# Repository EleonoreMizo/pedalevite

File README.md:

### We have moved!

**This page is now dead, there will not be any update anymore.**

**The new page is hosted here: https://gitlab.com/EleonoreMizo/pedalevite/**  
**Git repository address: https://gitlab.com/EleonoreMizo/pedalevite.git**

Please update your bookmarks! Repository is kept here for consistency with other projects but probably not indefinitely.

Pédale Vite — Multi-FX pedalboard
=================================

**Pédale Vite** is a DIY multi-FX pedalboard for guitar, bass or any other electric instrument.

It is based on a Raspberry Pi 4 and uses a custom audio board.

Key features:

- A large collection of effects within a single box: distortion, chorus, flanger, delay, reverb…
- Programs containing any free combination of the above effects
- 12 footswitches to activate the programs or other functionalities
- Fast and smooth transition between programs
- Up to 3 expression pedals to drive effects like wha, volume, LFOs…
- Infinite modulation possibilities
- Free effect routing
- Designed for stage and regular transport
- Silent and accurate tuner activated with a footswitch
- Standalone, no need for any external computer
- Building is easy and simple, can be reproduced and adapted by any person without specific skill
- Free software and hardware design
- And much more…

More information [here](http://ldesoras.free.fr/doc/articles/pedale-vite/pedale-vite-en.html).

The [/doc/](/doc/) folder contains everything you need to build the pedalboard.

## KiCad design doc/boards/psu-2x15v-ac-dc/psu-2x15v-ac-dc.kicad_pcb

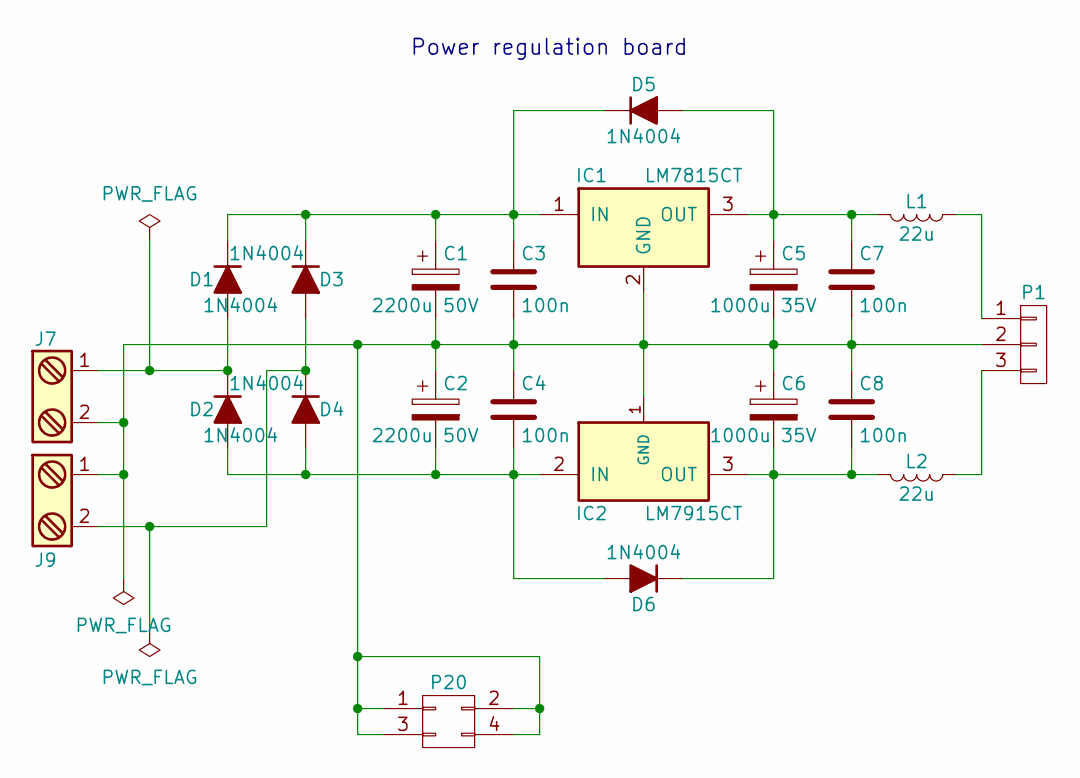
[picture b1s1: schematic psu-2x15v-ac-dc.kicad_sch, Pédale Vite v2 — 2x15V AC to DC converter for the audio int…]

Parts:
C1, C2: 2200u 50V; CP_Radial_D18.0mm_P7.50mm
C3, C4, C7, C8: 100n; C_Disc_D3.4mm_W2.1mm_P2.50mm
C5, C6: 1000u 35V; CP_Radial_D12.5mm_P5.00mm
D1, D2, D3, D4, D5, D6: 1N4004; D_DO-41_SOD81_P7.62mm_Horizontal
IC1: LM7815CT; TO-220_Vertical
IC2: LM7915CT; TO-220_Vertical
J7, J9: Screw_Terminal_1x02; TerminalBlock_Pheonix_MKDS1.5-2pol
L1, L2: 22u; Neosid_Inductor_Sd8
P1: CONN_01X03; Molex_KK-6410-03_03x2.54mm_Straight
P20: CONN_02X02; Pin_Header_Straight_2x02_Pitch2.54mm

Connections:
unnamed: C1.1, C3.1, D1.1 (K), D3.1 (K), D5.1 (K), IC1.1 (IN)
unnamed: C1.2, C2.1, C3.2, C4.1, C5.2, C6.1, C7.2, C8.1, IC1.2 (GND), IC2.1 (GND), J7.2, J9.1, P1.2, P20.1, P20.2, P20.3, P20.4
unnamed: C2.2, C4.2, D2.2 (A), D4.2 (A), D6.2 (A), IC2.2 (IN)
unnamed: C5.1, C7.1, D5.2 (A), IC1.3 (OUT), L1.2
unnamed: C6.2, C8.2, D6.1 (K), IC2.3 (OUT), L2.2
unnamed: D1.2 (A), D2.1 (K), J7.1
unnamed: D3.2 (A), D4.1 (K), J9.2
unnamed: L1.1, P1.1
unnamed: L2.1, P1.3

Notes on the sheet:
Power regulation board

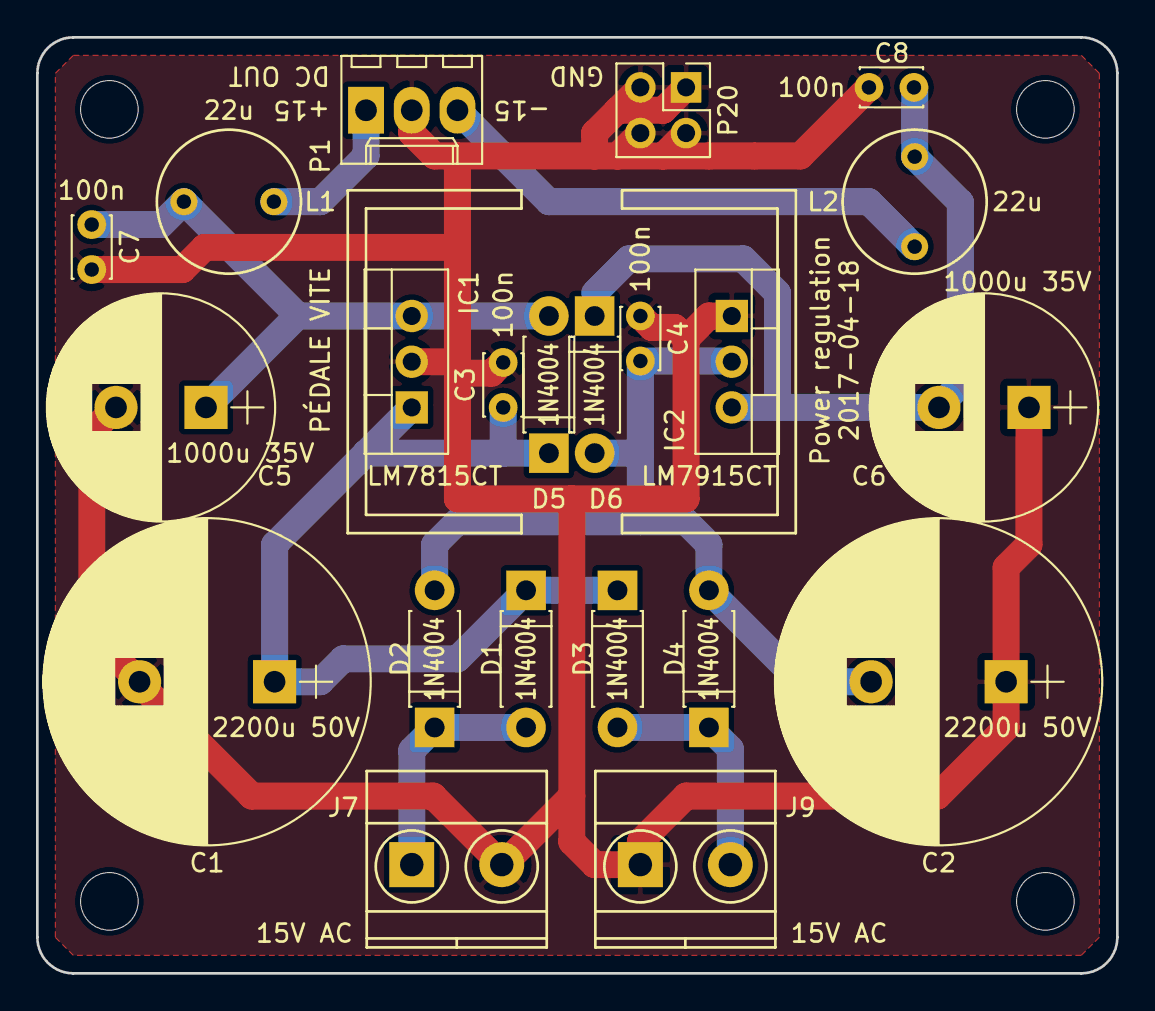
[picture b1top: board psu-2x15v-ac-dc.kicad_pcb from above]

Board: 2 copper layers, 60.0 x 52.0 mm, 22 parts (0 on the bottom side), 9 nets.

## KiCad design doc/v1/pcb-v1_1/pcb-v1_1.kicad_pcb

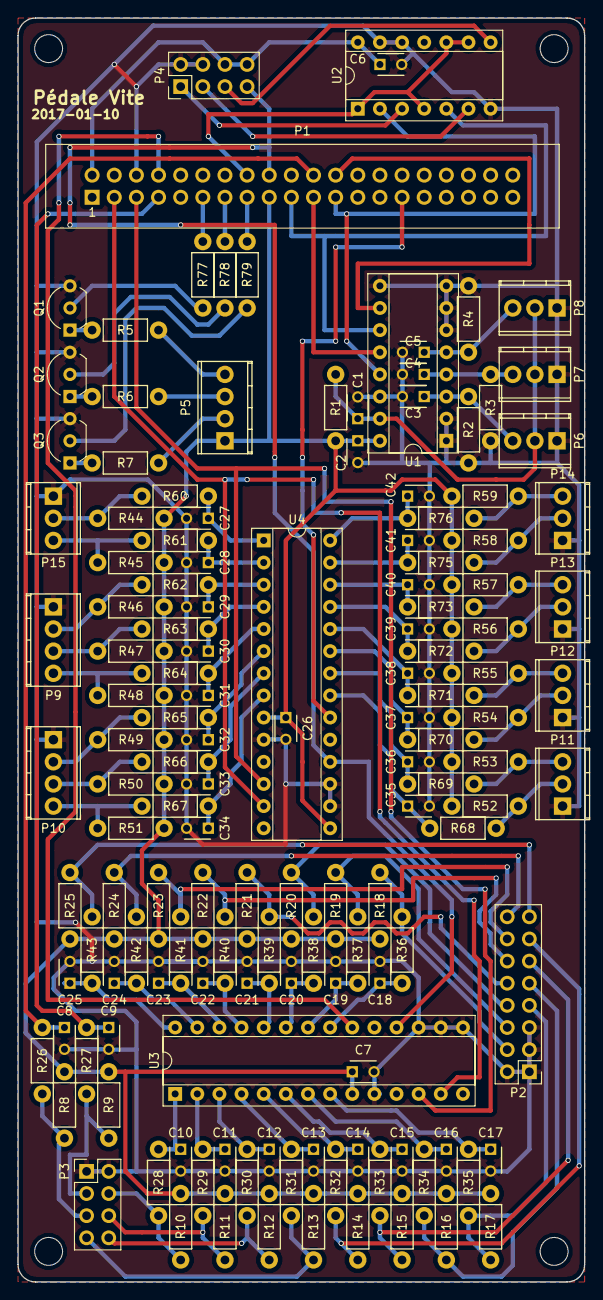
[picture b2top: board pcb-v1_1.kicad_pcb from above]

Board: 2 copper layers, 65.0 x 145.0 mm, 142 parts (0 on the bottom side), 100 nets.

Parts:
C1, C2: 1u; C_Disc_D3_P2.5
C3, C4, C5, C6, C7, C8, C9, C10, C11, C12, C13, C14, C15, C16, C17, C18, C19, C20, C21, C22, C23, C24, C25, C26, C27, C28, C29, C30, C31, C32, C33, C34, C35, C36, C37, C38, C39, C40, C41, C42: 100n; C_Disc_D3_P2.5
P1: Raspberry_Pi_2_3; IDC_Header_Straight_40pins
P2: CONN_02X08; Pin_Header_Straight_2x08_Pitch2.54mm
P3, P4: CONN_02X04; Pin_Header_Straight_2x04_Pitch2.54mm
P5, P9, P10: CONN_01X04; TerminalBlock_Pheonix_MPT-2.54mm_4pol
P6, P7, P8, P11, P12, P13, P14, P15: CONN_01X03; TerminalBlock_Pheonix_MPT-2.54mm_3pol
Q1, Q2, Q3: BC547; TO-92_Inline_Wide
R1: 1k5; Resistor_Horizontal_RM7mm
R2, R3, R4: 1M; Resistor_Horizontal_RM7mm
R5, R7: 56; Resistor_Horizontal_RM7mm
R6: 39; Resistor_Horizontal_RM7mm
R8, R9, R10, R11, R12, R13, R14, R15, R16, R17, R18, R19, R20, R21, R22, R23, R24, R25, R26, R27, R28, R29, R30, R31, R32, R33, R34, R35, R36, R37, R38, R39, R40, R41, R42, R43, R44, R45, R46, R47, R48, R49, R50, R51, R52, R53, R54, R55, R56, R57, R58, R59, R60, R61, R62, R63, R64, R65, R66, R67, R68, R69, R70, R71, R72, R73, R75, R76, R77, R78, R79: 10k; Resistor_Horizontal_RM7mm
U1: MCP3008; DIP-16_W7.62mm_Socket
U2: 74LS08; DIP-14_W7.62mm_Socket
U3, U4: MCP23017; DIP-28_W7.62mm_Socket

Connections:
+3V3: C2.1, C7.1, C26.1, P1.17, P5.1, R1.1, R8.1, R9.1, R10.1, R11.1, R12.1, R13.1, R14.1, R15.1, R16.1, R17.1, R18.1, R19.1, R20.1, R21.1, R22.1, R23.1, R24.1, R25.1, R44.1, R45.1, R46.1, R47.1, R48.1, R49.1, R50.1, R51.1, R52.1, R53.1, R54.1, R55.1, R56.1, R57.1, R58.1, R59.1, U1.16, U3.9, U4.9, U4.15
+5V: C6.1, P1.2, P4.6, P4.8, U2.14
Escape: C8.1, P1.22, R26.1
GND: C1.2, C2.2, C3.2, C4.2, C5.2, C6.2, C7.2, C8.2, C9.2, C10.2, C11.2, C12.2, C13.2, C14.2, C15.2, C16.2, C17.2, C18.2, C19.2, C20.2, C21.2, C22.2, C23.2, C24.2, C25.2, C26.2, C27.2, C28.2, C29.2, C30.2, C31.2, C32.2, C33.2, C34.2, C35.2, C36.2, C37.2, C38.2, C39.2, C40.2, C41.2, C42.2, P1.6, P2.1, P2.2, P2.3, P2.5, P3.1, P3.2, P4.2, P4.4, P6.1, P7.1, P8.1, P9.1, P10.1, P11.1, P12.1, P13.1, P14.1, P15.1, Q1.3, Q2.3, Q3.3, R2.2, R3.2, R4.2, U1.1, U1.2, U1.6, U1.7, U1.8, U1.9, U1.14, U2.7, U2.12, U2.13, U3.10, U3.15, U3.16, U3.17, U4.10, U4.16, U4.17
I2C_SCL: P1.5, U3.12, U4.12
I2C_SDA: P1.3, U3.13, U4.13
Int1: P1.8, U3.20
Int2: P1.29, U4.20
LED_0R: P1.11, R77.2
LED_1G: P1.13, R78.2
LED_2R: P1.15, R79.2
unnamed: C1.1, P6.2, P7.2, P8.2, R1.2, U1.15
unnamed: C3.1, P6.3, R2.1, U1.3
unnamed: C4.1, P7.3, R3.1, U1.4
unnamed: C5.1, P8.3, R4.1, U1.5
unnamed: C10.1, R28.1, U3.1
unnamed: C11.1, R29.1, U3.2
unnamed: C12.1, R30.1, U3.3
unnamed: C13.1, R31.1, U3.4
unnamed: C14.1, R32.1, U3.5
unnamed: C15.1, R33.1, U3.6
unnamed: C16.1, R34.1, U3.7
unnamed: C17.1, R35.1, U3.8
unnamed: C18.1, R36.1, U3.21
unnamed: C19.1, R37.1, U3.22
unnamed: C20.1, R38.1, U3.23
unnamed: C21.1, R39.1, U3.24
unnamed: C22.1, R40.1, U3.25
unnamed: C23.1, R41.1, U3.26
unnamed: C24.1, R42.1, U3.27
unnamed: C25.1, R43.1, U3.28
unnamed: C27.1, R60.1, U4.1
unnamed: C28.1, R61.1, U4.2
unnamed: C29.1, R62.1, U4.3
unnamed: C30.1, R63.1, U4.4
unnamed: C31.1, R64.1, U4.5
unnamed: C32.1, R65.1, U4.6
unnamed: C33.1, R66.1, U4.7
unnamed: C34.1, R67.1, U4.8
unnamed: C35.1, R68.1, U4.21
unnamed: C36.1, R69.1, U4.22
unnamed: C37.1, R70.1, U4.23
unnamed: C38.1, R71.1, U4.24
unnamed: C39.1, R72.1, U4.25
unnamed: C40.1, R73.1, U4.26
unnamed: C41.1, R75.1, U4.27
unnamed: C42.1, R76.1, U4.28
unnamed: P2.4, R18.2, R36.2
unnamed: P2.6, R19.2, R37.2
unnamed: P2.7, R17.2, R35.2
unnamed: P2.8, R20.2, R38.2
unnamed: P2.9, R16.2, R34.2
unnamed: P2.10, R21.2, R39.2
unnamed: P2.11, R15.2, R33.2
unnamed: P2.12, R22.2, R40.2
unnamed: P2.13, R14.2, R32.2
unnamed: P2.14, R23.2, R41.2
unnamed: P2.15, R25.2, R43.2
unnamed: P2.16, R24.2, R42.2
unnamed: P3.3, R9.2, R27.2
unnamed: P3.4, R10.2, R28.2
unnamed: P3.5, R8.2, R26.2
unnamed: P3.6, R11.2, R29.2
unnamed: P3.7, R13.2, R31.2
unnamed: P3.8, R12.2, R30.2
unnamed: P4.1, U2.3
unnamed: P4.3, U2.6
unnamed: P4.5, U2.8
unnamed: P5.2, R7.1
unnamed: P5.3, R6.1
unnamed: P5.4, R5.1
unnamed: P9.2, R46.2, R62.2
unnamed: P9.3, R47.2, R63.2
unnamed: P9.4, R48.2, R64.2
unnamed: P10.2, R49.2, R65.2
unnamed: P10.3, R50.2, R66.2
unnamed: P10.4, R51.2, R67.2
unnamed: P11.2, R52.2, R68.2
unnamed: P11.3, R53.2, R69.2
unnamed: P12.2, R54.2, R70.2
unnamed: P12.3, R55.2, R71.2
unnamed: P13.2, R56.2, R72.2
unnamed: P13.3, R57.2, R73.2
unnamed: P14.2, R58.2, R75.2
unnamed: P14.3, R59.2, R76.2
unnamed: P15.2, R44.2, R60.2
unnamed: P15.3, R45.2, R61.2
unnamed: Q1.1, R5.2
unnamed: Q1.2, R77.1
unnamed: Q2.1, R6.2
unnamed: Q2.2, R78.1
unnamed: Q3.1, R7.2
unnamed: Q3.2, R79.1
SPI_CE0: P1.24, U1.10
SPI_MISO: P1.21, U1.12
SPI_MOSI: P1.19, U1.11, U2.5
SPI_SCLK: P1.23, U1.13, U2.2
Select: C9.1, P1.7, R27.1
~Disp_CS: P1.16, U2.1, U2.4, U2.9, U2.10
~Reset: P1.18, P4.7, U3.18, U4.18

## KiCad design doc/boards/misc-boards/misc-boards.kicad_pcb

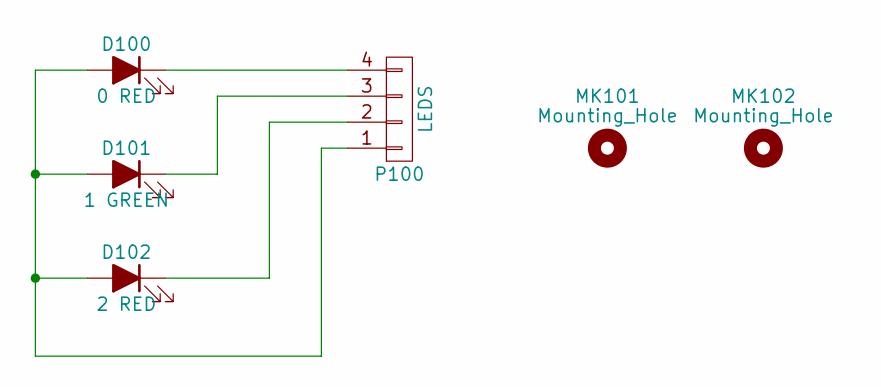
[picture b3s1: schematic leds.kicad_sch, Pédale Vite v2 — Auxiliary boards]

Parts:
D100: 0 RED; LED_D5.0mm
D101: 1 GREEN; LED_D5.0mm
D102: 2 RED; LED_D5.0mm
MK101, MK102: Mounting_Hole; MountingHole_3.2mm_M3
P100: LEDS; Socket_MOLEX-KK-RM2-54mm_Lock_4pin_straight

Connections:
unnamed: D100.1 (K), P100.4
unnamed: D100.2 (A), D101.2 (A), D102.2 (A), P100.1
unnamed: D101.1 (K), P100.3
unnamed: D102.1 (K), P100.2

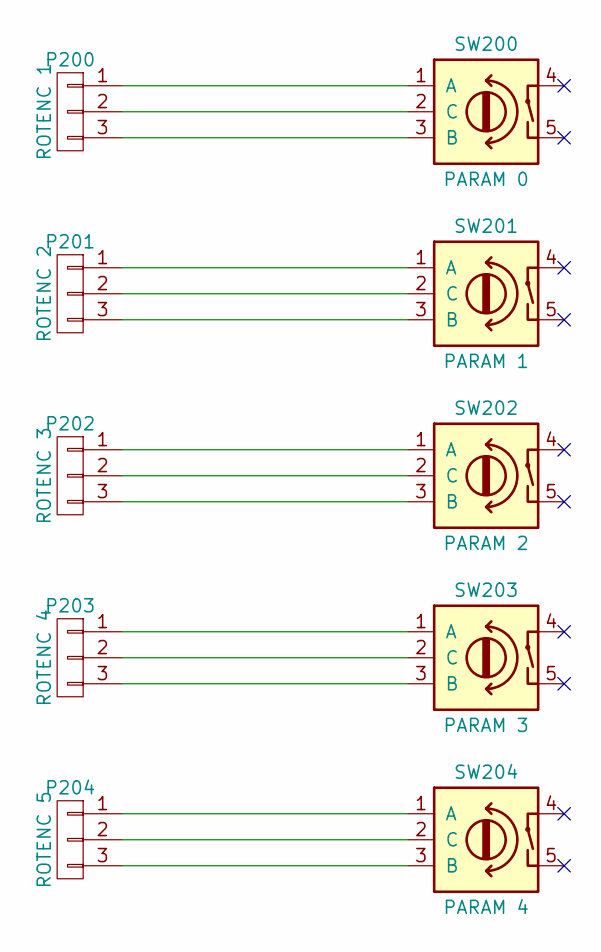
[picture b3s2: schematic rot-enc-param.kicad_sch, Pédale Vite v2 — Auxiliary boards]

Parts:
P200: ROTENC 1; Socket_MOLEX-KK-RM2-54mm_Lock_3pin_straight
P201: ROTENC 2; Socket_MOLEX-KK-RM2-54mm_Lock_3pin_straight
P202: ROTENC 3; Socket_MOLEX-KK-RM2-54mm_Lock_3pin_straight
P203: ROTENC 4; Socket_MOLEX-KK-RM2-54mm_Lock_3pin_straight
P204: ROTENC 5; Socket_MOLEX-KK-RM2-54mm_Lock_3pin_straight
SW200: PARAM 0; RotaryEncoder_Bourns_PEC11R-Switch_Vertical
SW201: PARAM 1; RotaryEncoder_Bourns_PEC11R-Switch_Vertical
SW202: PARAM 2; RotaryEncoder_Bourns_PEC11R-Switch_Vertical
SW203: PARAM 3; RotaryEncoder_Bourns_PEC11R-Switch_Vertical
SW204: PARAM 4; RotaryEncoder_Bourns_PEC11R-Switch_Vertical

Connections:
unnamed: P200.1, SW200.1 (A)
unnamed: P200.2, SW200.2 (C)
unnamed: P200.3, SW200.3 (B)
unnamed: P201.1, SW201.1 (A)
unnamed: P201.2, SW201.2 (C)
unnamed: P201.3, SW201.3 (B)
unnamed: P202.1, SW202.1 (A)
unnamed: P202.2, SW202.2 (C)
unnamed: P202.3, SW202.3 (B)
unnamed: P203.1, SW203.1 (A)
unnamed: P203.2, SW203.2 (C)
unnamed: P203.3, SW203.3 (B)
unnamed: P204.1, SW204.1 (A)
unnamed: P204.2, SW204.2 (C)
unnamed: P204.3, SW204.3 (B)

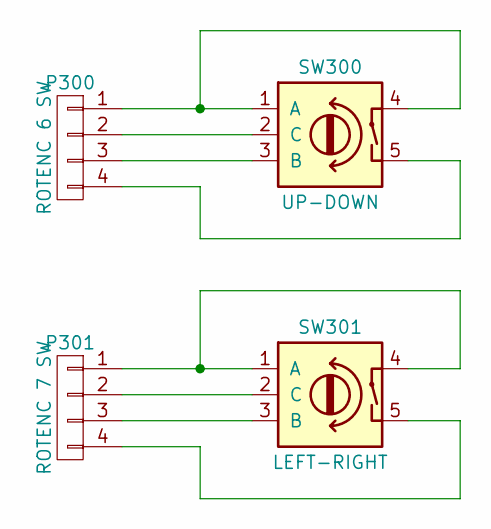
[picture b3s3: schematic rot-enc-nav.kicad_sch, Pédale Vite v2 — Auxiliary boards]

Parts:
P300: ROTENC 6 SW; Socket_MOLEX-KK-RM2-54mm_Lock_4pin_straight
P301: ROTENC 7 SW; Socket_MOLEX-KK-RM2-54mm_Lock_4pin_straight
SW300: UP-DOWN; RotaryEncoder_Bourns_PEC11R-Switch_Vertical
SW301: LEFT-RIGHT; RotaryEncoder_Bourns_PEC11R-Switch_Vertical

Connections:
unnamed: P300.1, SW300.1 (A), SW300.4
unnamed: P300.2, SW300.2 (C)
unnamed: P300.3, SW300.3 (B)
unnamed: P300.4, SW300.5
unnamed: P301.1, SW301.1 (A), SW301.4
unnamed: P301.2, SW301.2 (C)
unnamed: P301.3, SW301.3 (B)
unnamed: P301.4, SW301.5

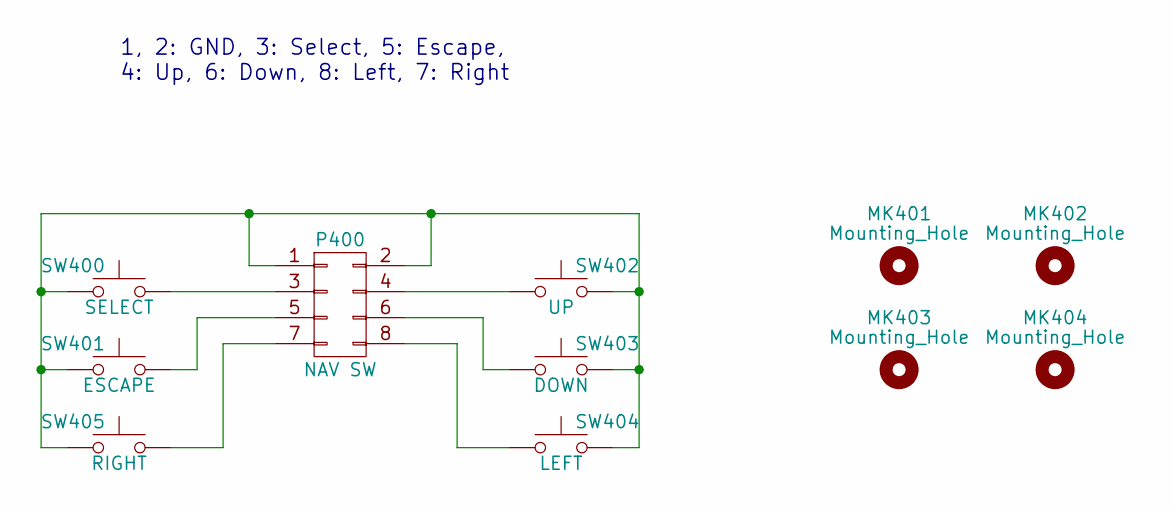
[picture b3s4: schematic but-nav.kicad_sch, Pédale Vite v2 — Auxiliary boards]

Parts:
MK401, MK402, MK403, MK404: Mounting_Hole; MountingHole_3.2mm_M3
P400: NAV SW; Pin_Header_Straight_2x04_Pitch2.54mm
SW400: SELECT; SW_MEC_5GTH9
SW401: ESCAPE; SW_MEC_5GTH9
SW402: UP; SW_MEC_5GTH9
SW403: DOWN; SW_MEC_5GTH9
SW404: LEFT; SW_MEC_5GTH9
SW405: RIGHT; SW_MEC_5GTH9

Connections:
unnamed: P400.1, P400.2, SW400.2, SW401.2, SW402.2, SW403.2, SW404.2, SW405.2
unnamed: P400.3, SW400.1
unnamed: P400.4, SW402.1
unnamed: P400.5, SW401.1
unnamed: P400.6, SW403.1
unnamed: P400.7, SW405.1
unnamed: P400.8, SW404.1

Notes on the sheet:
1, 2: GND, 3: Select, 5: Escape, 4: Up, 6: Down, 8: Left, 7: Right

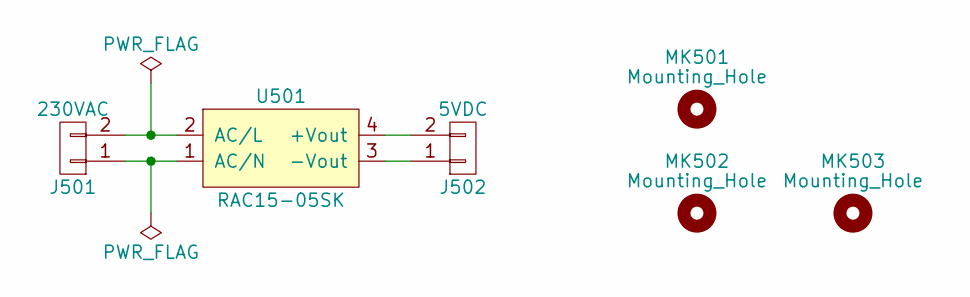
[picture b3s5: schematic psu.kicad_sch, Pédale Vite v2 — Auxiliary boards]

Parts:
J501: 230VAC; TerminalBlock_Altech_AK300-2_P5.00mm
J502: 5VDC; TerminalBlock_Altech_AK300-2_P5.00mm
MK501, MK502, MK503: Mounting_Hole; MountingHole_3.2mm_M3
U501: RAC15-05SK; Converter_ACDC_RECOM_RAC15-xxSK_THT

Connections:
unnamed: J501.1, U501.1 (AC/N)
unnamed: J501.2, U501.2 (AC/L)
unnamed: J502.1, U501.3 (-Vout)
unnamed: J502.2, U501.4 (+Vout)

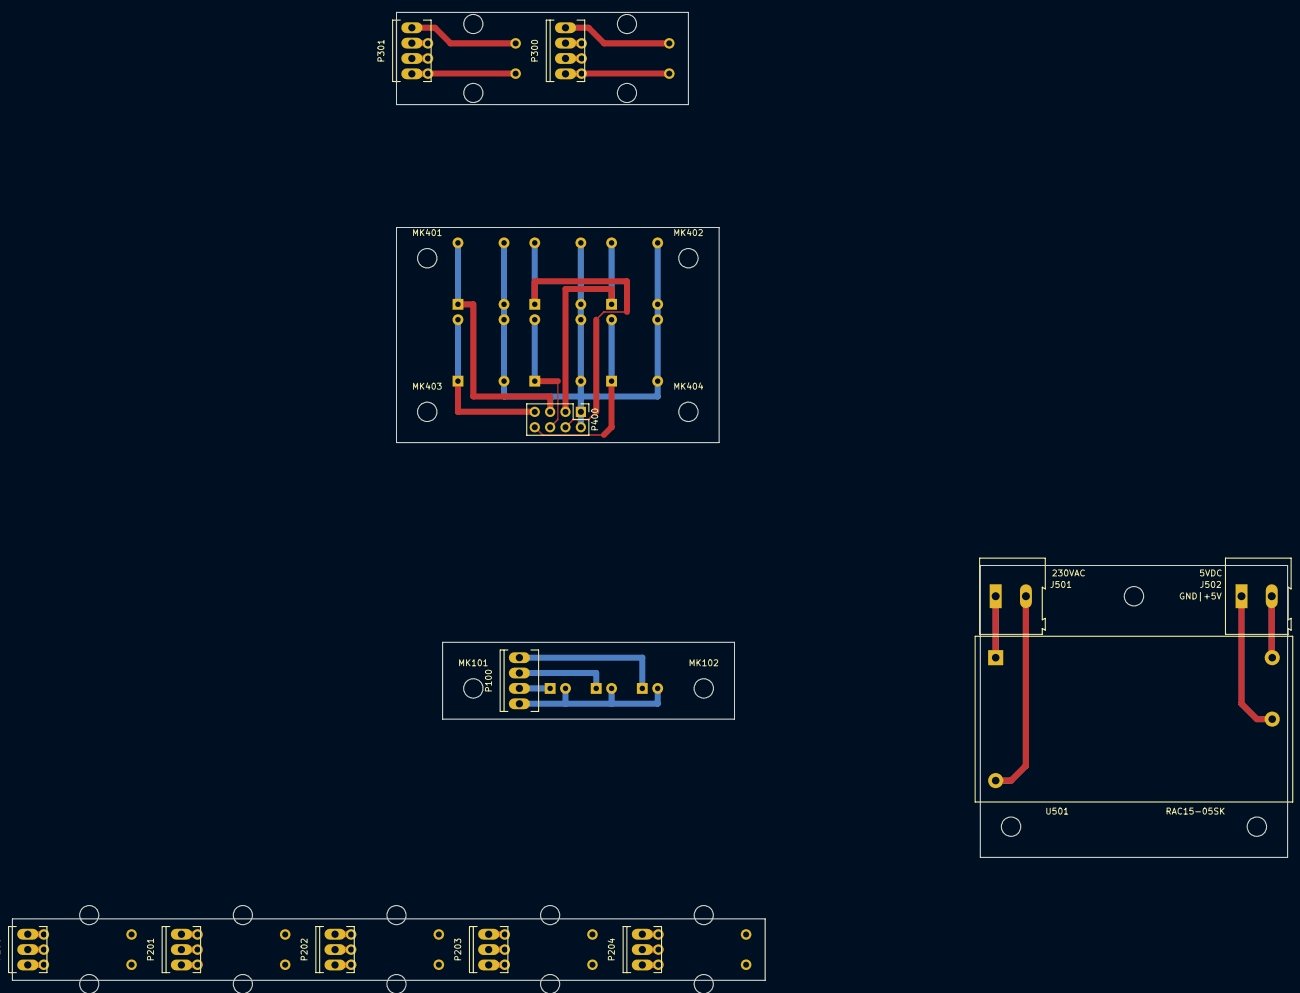
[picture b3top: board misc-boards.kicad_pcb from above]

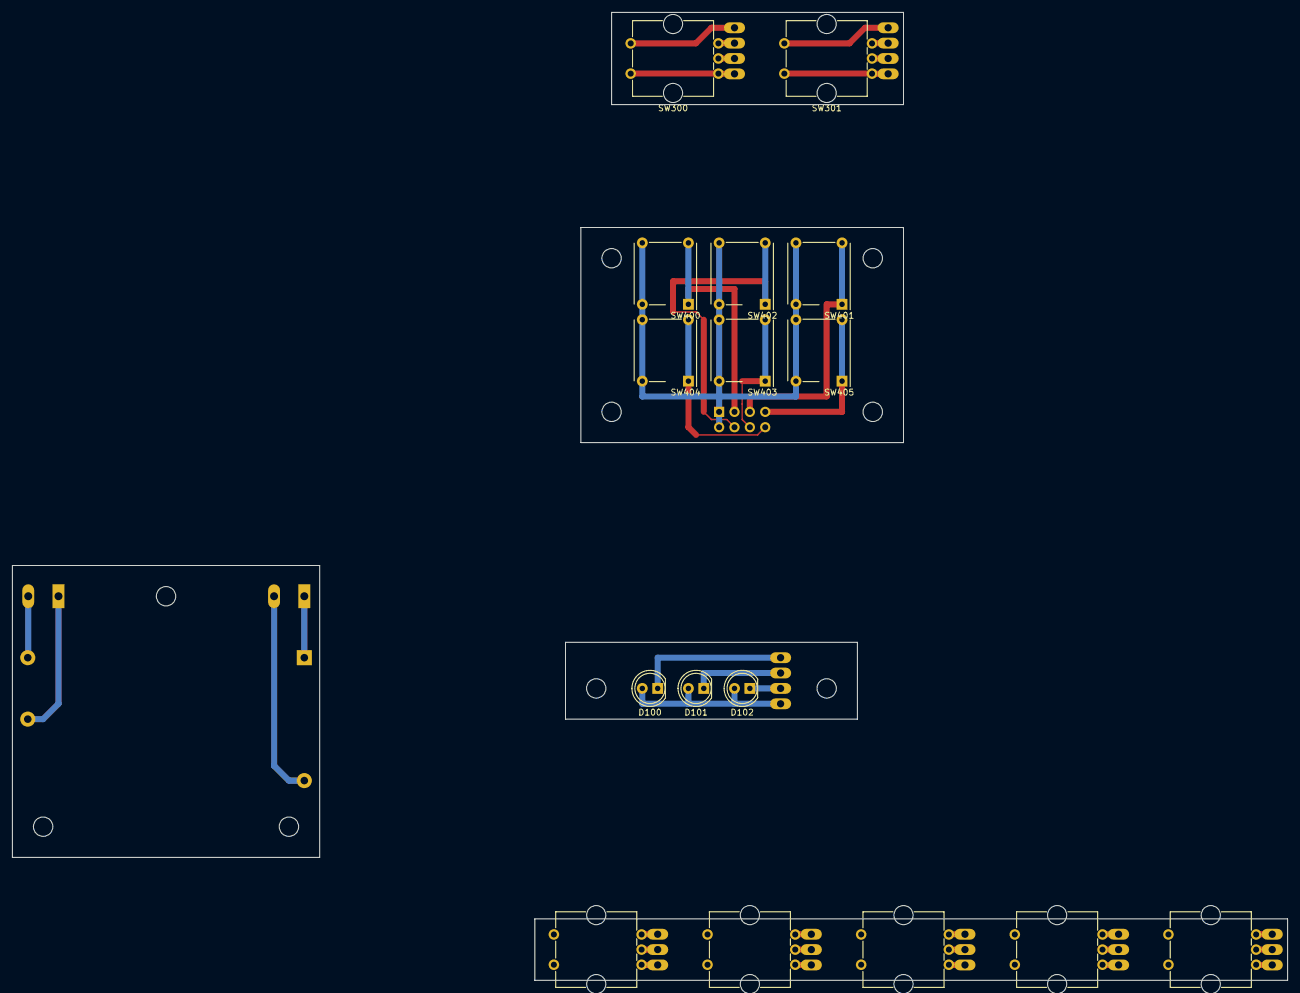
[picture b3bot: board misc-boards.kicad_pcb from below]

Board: 2 copper layers, 210.8 x 160.0 mm, 37 parts (16 on the bottom side), 38 nets.

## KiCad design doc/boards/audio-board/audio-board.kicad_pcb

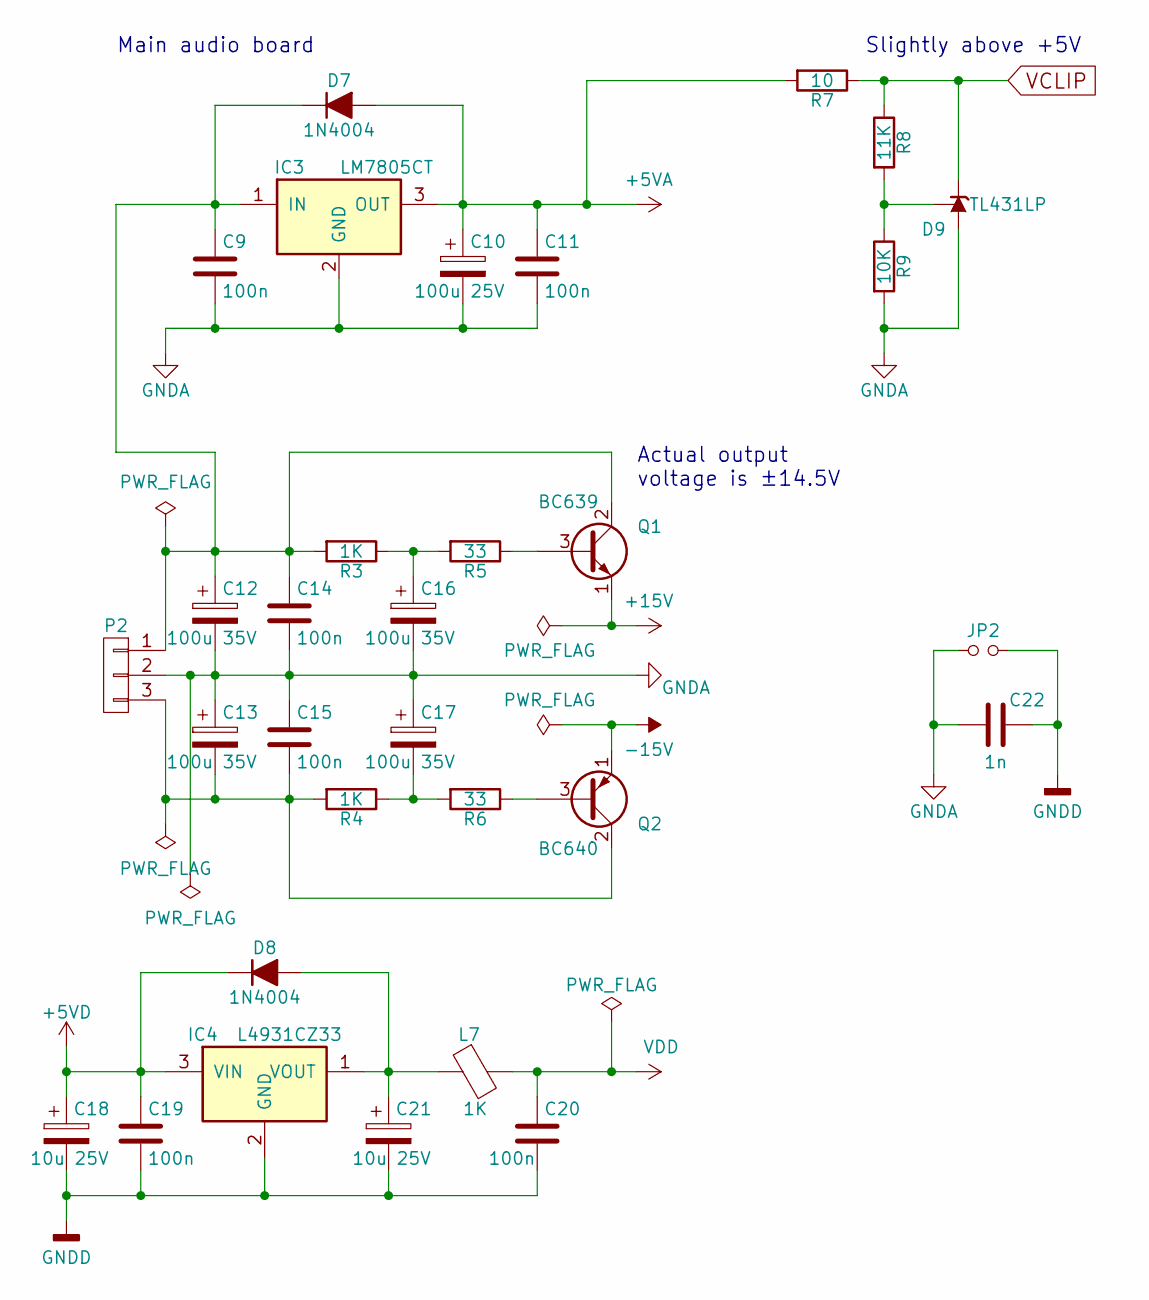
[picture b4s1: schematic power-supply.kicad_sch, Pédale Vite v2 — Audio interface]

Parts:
C9, C11, C14, C15, C19, C20: 100n; C_Disc_D3.4mm_W2.1mm_P2.50mm
C10: 100u 25V; CP_Radial_D6.3mm_P2.50mm
C12, C13, C16, C17: 100u 35V; CP_Radial_D8.0mm_P3.50mm
C18, C21: 10u 25V; CP_Radial_D5.0mm_P2.00mm
C22: 1n; C_Disc_D3.4mm_W2.1mm_P2.50mm
D7, D8: 1N4004; D_DO-41_SOD81_P7.62mm_Horizontal
D9: TL431LP; TO-92_Inline_Wide
IC3: LM7805CT; TO-220_Vertical
IC4: L4931CZ33; TO-92_Inline_Wide
JP2: Jumper_NO_Small; Pin_Header_Straight_1x02_Pitch2.54mm
L7: 1K; CP_Radial_Tantal_D6.0mm_P5.00mm
P2: CONN_01X03; Molex_KK-6410-03_03x2.54mm_Straight
Q1: BC639; TO-92_Inline_Wide
Q2: BC640; TO-92_Inline_Wide
R3, R4: 1K; R_Axial_DIN0207_L6.3mm_D2.5mm_P7.62mm_Horizontal
R5, R6: 33; R_Axial_DIN0207_L6.3mm_D2.5mm_P7.62mm_Horizontal
R7: 10; R_Axial_DIN0207_L6.3mm_D2.5mm_P7.62mm_Horizontal
R8: 11K; R_Axial_DIN0207_L6.3mm_D2.5mm_P7.62mm_Horizontal
R9: 10K; R_Axial_DIN0207_L6.3mm_D2.5mm_P7.62mm_Horizontal

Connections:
+5VA: C10.1, C11.1, D7.2 (A), IC3.3 (OUT), R7.2; also elsewhere on the board
+5VD: C18.1, C19.1, D8.1 (K), IC4.3 (VIN); also elsewhere on the board
-15V: Q2.1 (E); also elsewhere on the board
GNDA: C9.2, C10.2, C11.2, C12.2, C13.1, C14.2, C15.1, C16.2, C17.1, C22.2, D9.2 (A), IC3.2 (GND), JP2.1, P2.2, R9.2; also elsewhere on the board
GNDD: C18.2, C19.2, C20.2, C21.2, C22.1, IC4.2 (GND), JP2.2; also elsewhere on the board
unnamed: C9.1, C12.1, C14.1, D7.1 (K), IC3.1 (IN), P2.1, Q1.2 (C), R3.2
unnamed: C13.2, C15.2, P2.3, Q2.2 (C), R4.2
unnamed: C16.1, R3.1, R5.2
unnamed: C17.2, R4.1, R6.2
unnamed: C21.1, D8.2 (A), IC4.1 (VOUT), L7.1
unnamed: D9.1 (REF), R8.2, R9.1
unnamed: Q1.3 (B), R5.1
unnamed: Q2.3 (B), R6.1
VCLIP: D9.3 (K), R7.1, R8.1; also elsewhere on the board
VDD: C20.1, L7.2; also elsewhere on the board

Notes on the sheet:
Main audio board
Actual output voltage is ±14.5V
Slightly above +5V

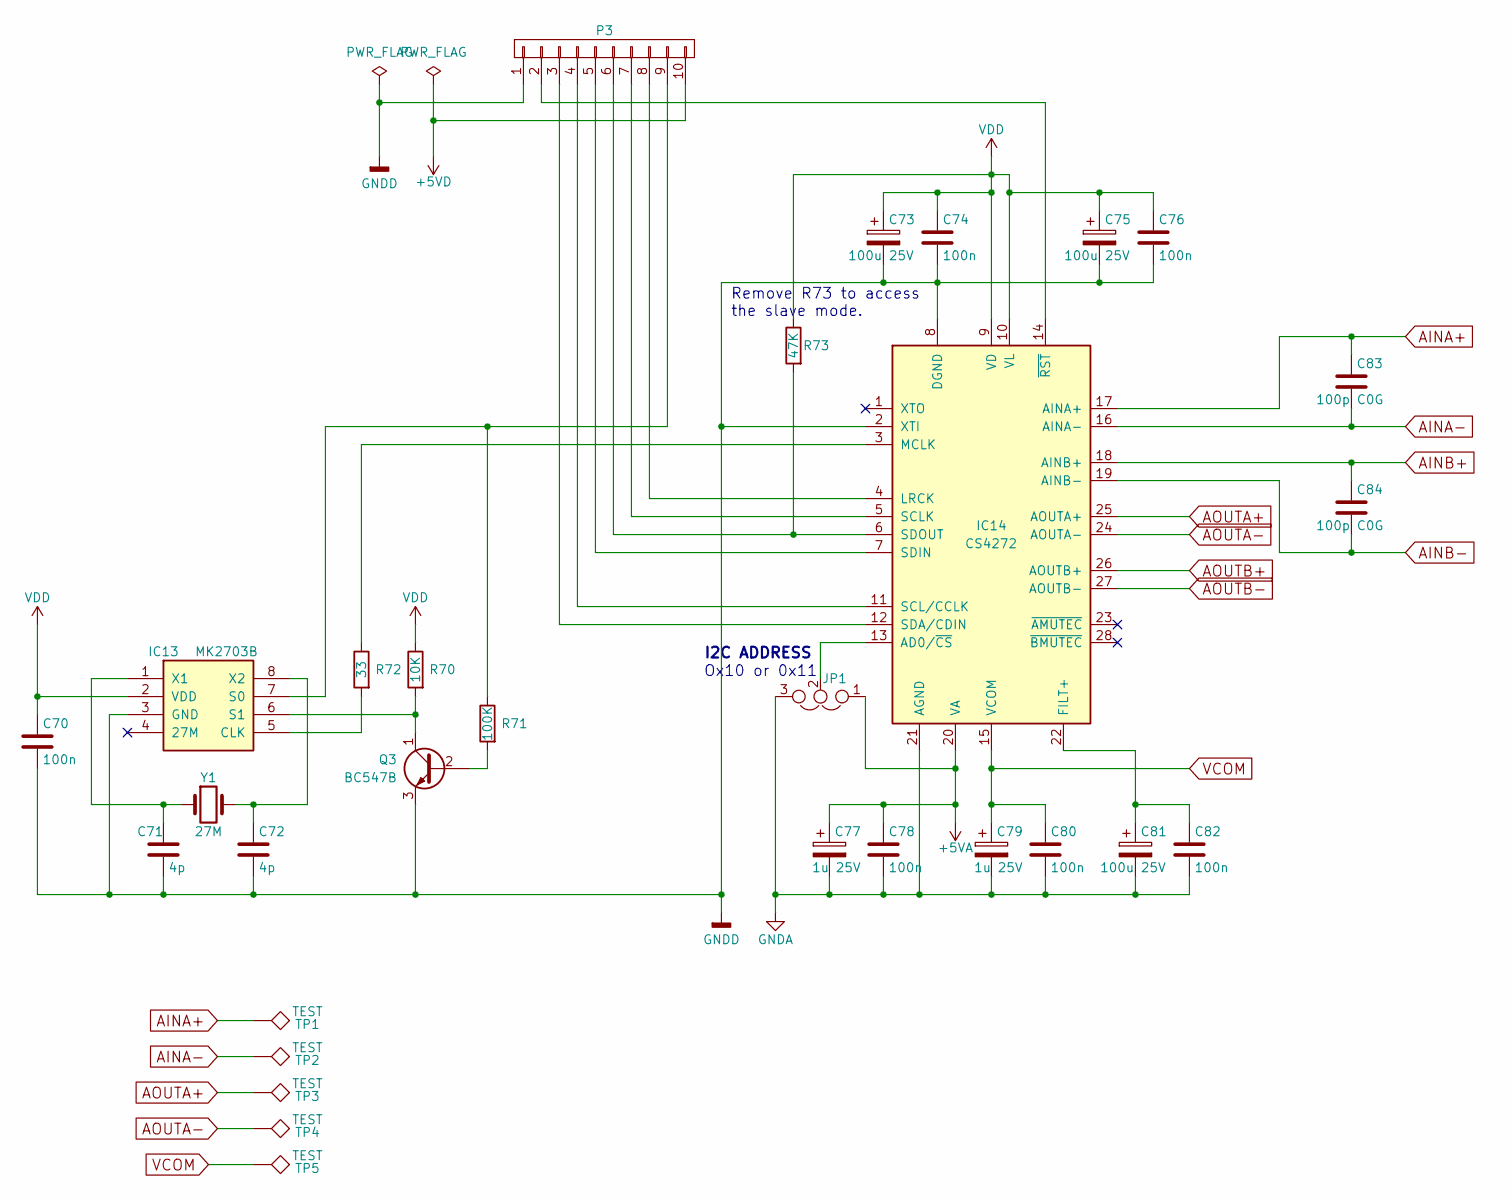
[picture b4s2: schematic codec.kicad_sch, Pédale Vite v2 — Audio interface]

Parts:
C70, C74, C76, C78, C80, C82: 100n; C_Disc_D3.4mm_W2.1mm_P2.50mm
C71, C72: 4p; C_Disc_D3.4mm_W2.1mm_P2.50mm
C73, C75, C81: 100u 25V; CP_Radial_D6.3mm_P2.50mm
C77, C79: 1u 25V; CP_Radial_D5.0mm_P2.00mm
C83, C84: 100p C0G; C_Disc_D3.4mm_W2.1mm_P2.50mm
IC13: MK2703B; SOIC-8_3.9x4.9mm_Pitch1.27mm
IC14: CS4272; TSSOP-28_4.4x9.7mm_Pitch0.65mm_manual_soldering
JP1: Jumper_NC_Dual; Pin_Header_Straight_1x03_Pitch2.54mm
P3: CONN_01X10; Pin_Header_Straight_1x10_Pitch2.54mm
Q3: BC547B; TO-92_Inline_Wide
R70: 10K; R_Axial_DIN0207_L6.3mm_D2.5mm_P7.62mm_Horizontal
R71: 100K; R_Axial_DIN0207_L6.3mm_D2.5mm_P7.62mm_Horizontal
R72: 33; R_Axial_DIN0207_L6.3mm_D2.5mm_P2.54mm_Vertical
R73: 47K; R_Axial_DIN0207_L6.3mm_D2.5mm_P7.62mm_Horizontal
TP1, TP2, TP3, TP4, TP5: TEST; Measurement_Point_Round-TH_Small
Y1: 27M; Crystal_HC49-U_Vertical

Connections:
+5VA: C77.1, C78.1, IC14.20 (VA), JP1.1; also elsewhere on the board
+5VD: P3.10; also elsewhere on the board
AINA+: C83.1, IC14.17 (AINA+), TP1.1; also elsewhere on the board
AINA-: C83.2, IC14.16 (AINA-), TP2.1; also elsewhere on the board
AINB+: C84.1, IC14.18 (AINB+); also elsewhere on the board
AINB-: C84.2, IC14.19 (AINB-); also elsewhere on the board
AOUTA+: IC14.25 (AOUTA+), TP3.1; also elsewhere on the board
AOUTA-: IC14.24 (AOUTA-), TP4.1; also elsewhere on the board
AOUTB+: IC14.26 (AOUTB+); also elsewhere on the board
AOUTB-: IC14.27 (AOUTB-); also elsewhere on the board
GNDA: C77.2, C78.2, C79.2, C80.2, C81.2, C82.2, IC14.21 (AGND), JP1.3; also elsewhere on the board
GNDD: C70.2, C71.2, C72.2, C73.2, C74.2, C75.2, C76.2, IC13.3 (GND), IC14.2 (XTI), IC14.8 (DGND), P3.1, Q3.3 (E); also elsewhere on the board
unnamed: C71.1, IC13.1 (X1), Y1.1
unnamed: C72.1, IC13.8 (X2), Y1.2
unnamed: C81.1, C82.1, IC14.22 (FILT+)
unnamed: IC13.5 (CLK), R72.2
unnamed: IC13.6 (S1), Q3.1 (C), R70.2
unnamed: IC13.7 (S0), P3.9, R71.1
unnamed: IC14.3 (MCLK), R72.1
unnamed: IC14.4 (LRCK), P3.8
unnamed: IC14.5 (SCLK), P3.7
unnamed: IC14.6 (SDOUT), P3.6, R73.2
unnamed: IC14.7 (SDIN), P3.5
unnamed: IC14.11 (SCL/CCLK), P3.4
unnamed: IC14.12 (SDA/CDIN), P3.3
unnamed: IC14.13 (AD0/~CS), JP1.2
unnamed: IC14.14 (~RST), P3.2
unnamed: Q3.2 (B), R71.2
VCOM: C79.1, C80.1, IC14.15 (VCOM), TP5.1; also elsewhere on the board
VDD: C70.1, C73.1, C74.1, C75.1, C76.1, IC13.2 (VDD), IC14.9 (VD), IC14.10 (VL), R70.1, R73.1; also elsewhere on the board

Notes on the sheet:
Ox10 or 0x11
I2C ADDRESS
Remove R73 to access the slave mode.

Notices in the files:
doc/boards/misc-boards/but-nav.kicad_sch:
Licensed under WTFPL v2 / CC0
